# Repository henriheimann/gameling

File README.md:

# Gameling

A primitive handheld gaming console I build just for the sake of it. Comes with a backlight monochrome Nokia 5110 clip on display with a resolution of 84 times 48 pixels, 12 buttons that can be individually lit up and a piezo buzzer.

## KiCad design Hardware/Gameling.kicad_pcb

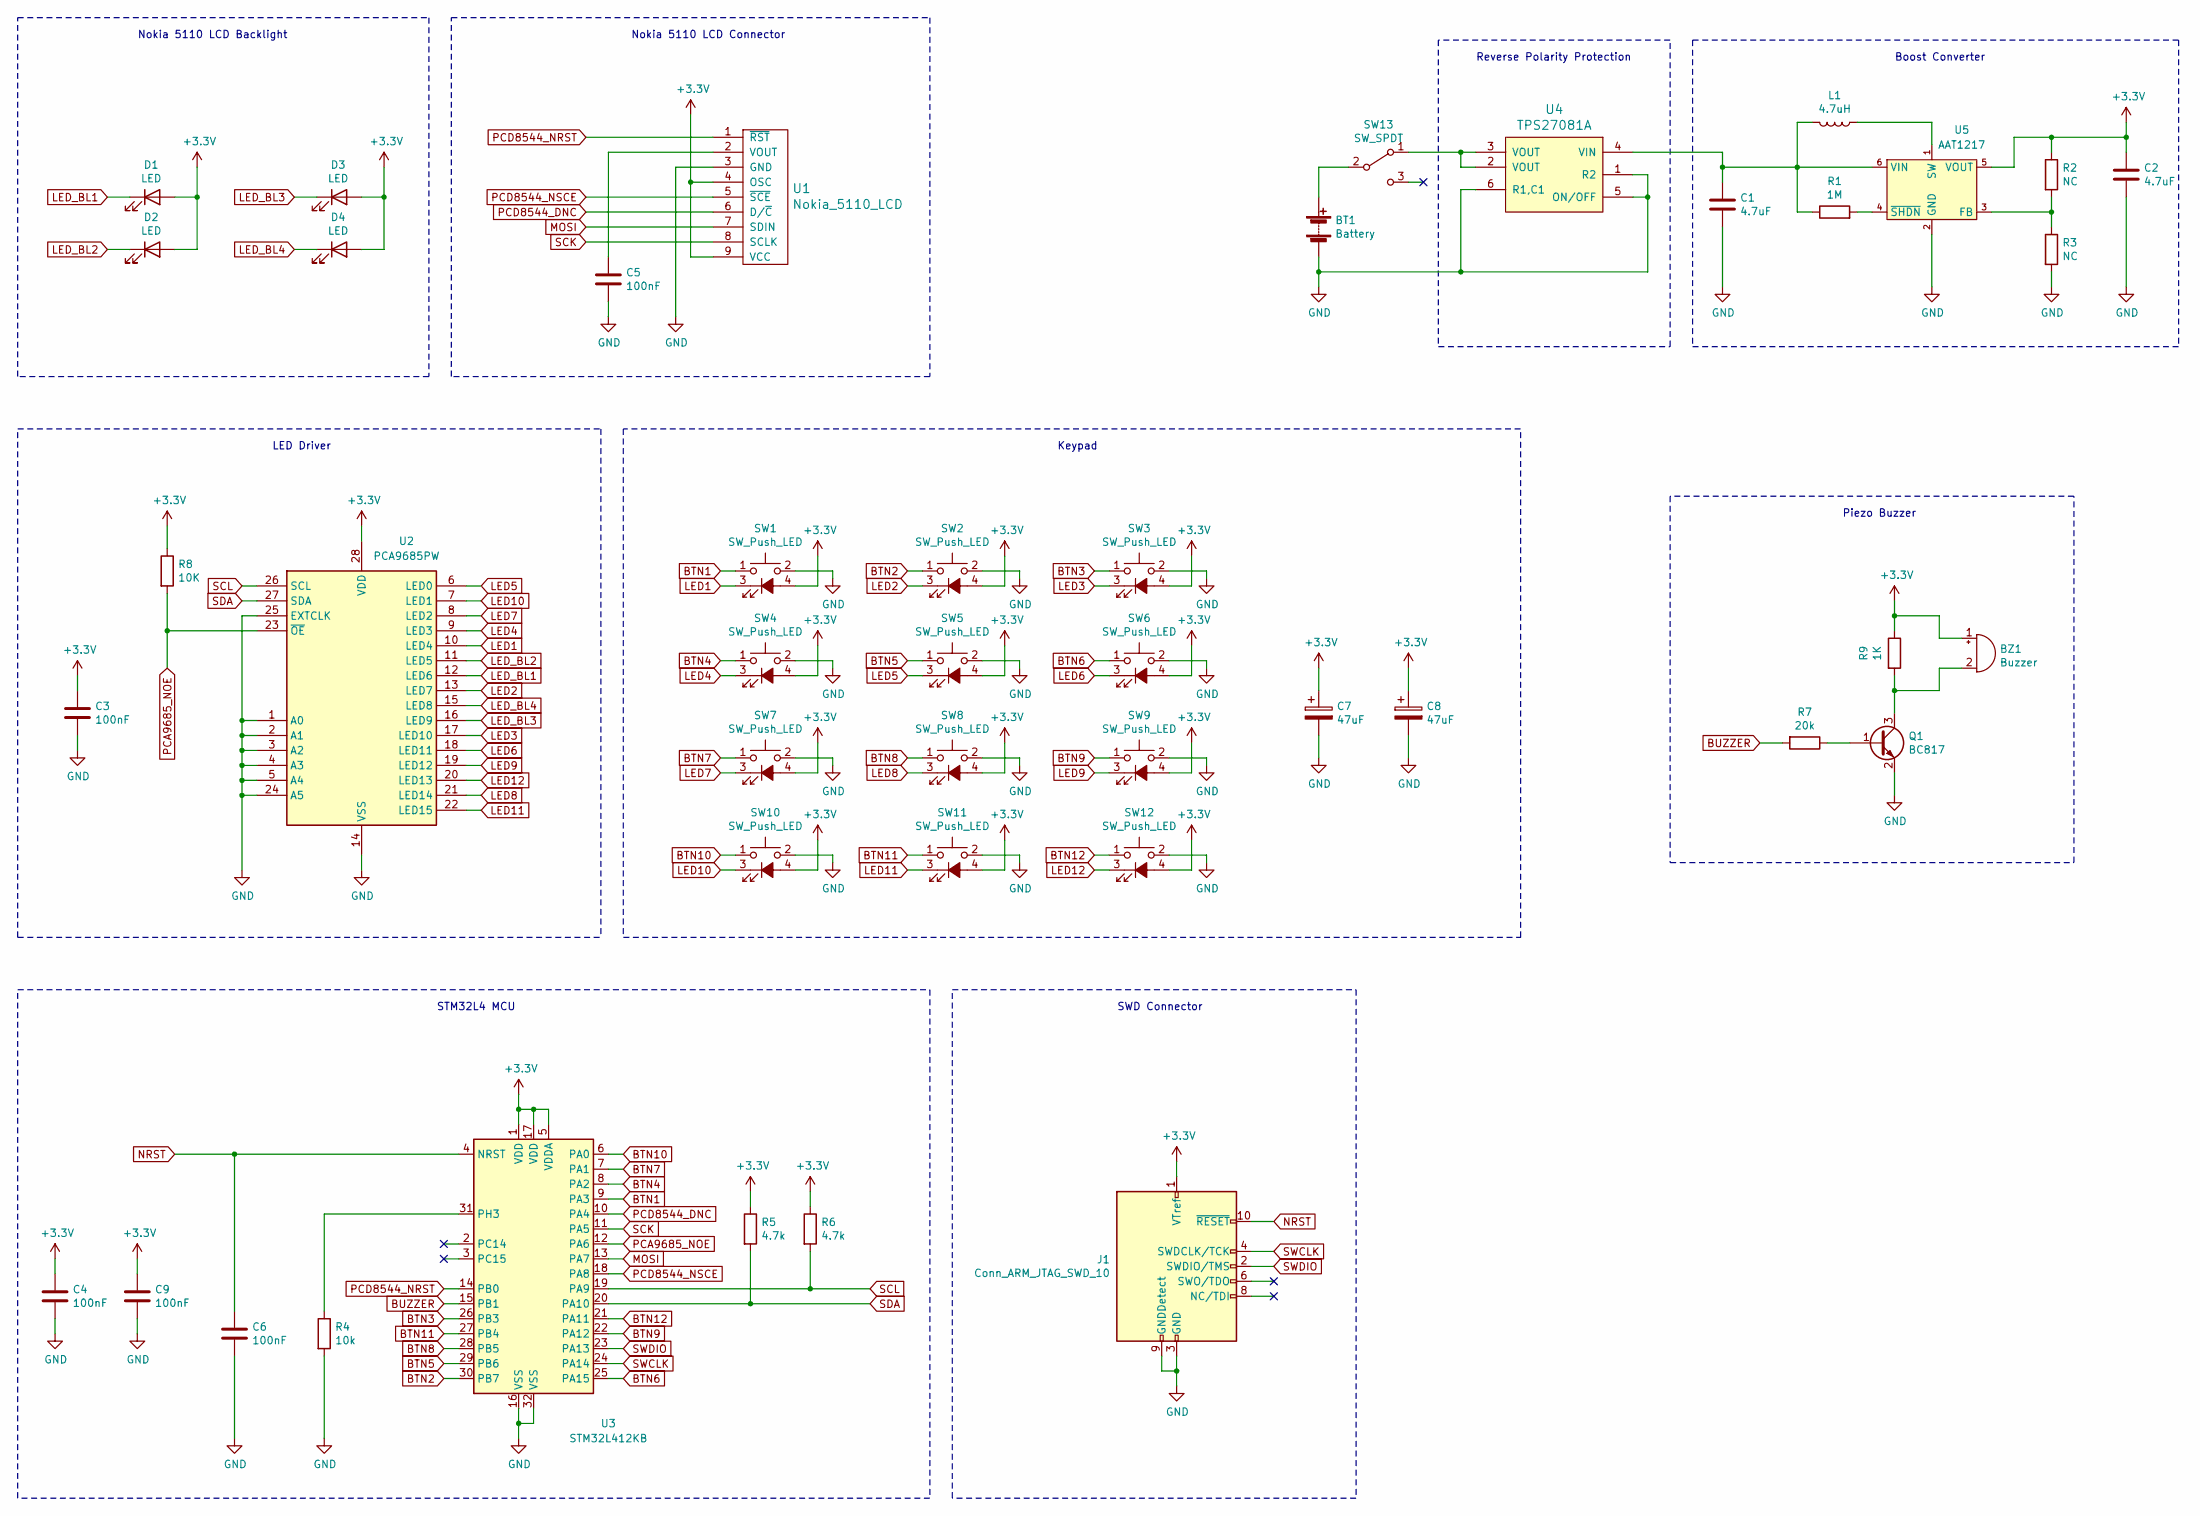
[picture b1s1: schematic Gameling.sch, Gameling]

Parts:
BT1: Battery; BatteryHolder_Keystone_2468_2xAAA_NoSilkscreen
BZ1: Buzzer; Buzzer_CUI_CPT-9019S-SMT_With3DModel
C1, C2: 4.7uF; C_0805_2012Metric_Pad1.15x1.40mm_HandSolder
C3, C4, C5, C6, C9: 100nF; C_0805_2012Metric_Pad1.15x1.40mm_HandSolder
C7, C8: 47uF; CP_Elec_4x4.5
D1, D2, D3, D4: LED; D_0805_2012Metric_Pad1.15x1.40mm_HandSolder_NoSilkscreen
J1: Conn_ARM_JTAG_SWD_10; Amphenol_FCI_ShroudedSocket_2x05_P1.27mm_Vertical_SMD
L1: 4.7uH; L_Bourns-SRN4018_With3DModel
Q1: BC817; SOT-23
R1: 1M; R_0805_2012Metric_Pad1.15x1.40mm_HandSolder
R2, R3: NC; R_0805_2012Metric_Pad1.15x1.40mm_HandSolder
R4: 10k; R_0805_2012Metric_Pad1.15x1.40mm_HandSolder
R5, R6: 4.7k; R_0805_2012Metric_Pad1.15x1.40mm_HandSolder
R7: 20k; R_0805_2012Metric_Pad1.15x1.40mm_HandSolder
R8: 10K; R_0805_2012Metric_Pad1.15x1.40mm_HandSolder
R9: 1K; R_0805_2012Metric_Pad1.15x1.40mm_HandSolder
SW1, SW2, SW3, SW4, SW5, SW6, SW7, SW8, SW9, SW10, SW11, SW12: SW_Push_LED; Generic_LED_Tactile_Button
SW13: SW_SPDT; SW_CuK_OS102011MA1QN1_SPDT_Angled_With3DModel_NoSilkscreen
U1: Nokia_5110_LCD; Nokia_5110-3310_LCD_NoSilkscreen
U2: PCA9685PW; TSSOP-28_4.4x9.7mm_P0.65mm
U3: STM32L412KB; LQFP-32_7x7mm_P0.8mm
U4: TPS27081A; TSOT-23-6_HandSoldering
U5: AAT1217; TSOT-23-6_HandSoldering

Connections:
+3V3: BZ1.1 (-), C2.1, C3.1, C4.1, C7.1, C8.1, C9.1, D1.2 (A), D2.2 (A), D3.2 (A), D4.2 (A), J1.1 (VTref), R2.1, R5.1, R6.1, R8.1, R9.1, SW1.4 (A), SW2.4 (A), SW3.4 (A), SW4.4 (A), SW5.4 (A), SW6.4 (A), SW7.4 (A), SW8.4 (A), SW9.4 (A), SW10.4 (A), SW11.4 (A), SW12.4 (A), U1.4 (OSC), U1.9 (VCC), U2.28 (VDD), U3.1 (VDD), U3.5 (VDDA), U3.17 (VDD), U5.5 (VOUT)
BTN1: SW1.1, U3.9 (PA3)
BTN2: SW2.1, U3.30 (PB7)
BTN3: SW3.1, U3.26 (PB3)
BTN4: SW4.1, U3.8 (PA2)
BTN5: SW5.1, U3.29 (PB6)
BTN6: SW6.1, U3.25 (PA15)
BTN7: SW7.1, U3.7 (PA1)
BTN8: SW8.1, U3.28 (PB5)
BTN9: SW9.1, U3.22 (PA12)
BTN10: SW10.1, U3.6 (PA0)
BTN11: SW11.1, U3.27 (PB4)
BTN12: SW12.1, U3.21 (PA11)
BUZZER: R7.2, U3.15 (PB1)
GND: BT1.2 (-), C1.2, C2.2, C3.2, C4.2, C5.2, C6.2, C7.2, C8.2, C9.2, J1.3 (GND), J1.5 (GND), J1.9 (GNDDetect), Q1.2 (E), R3.2, R4.2, SW1.2, SW2.2, SW3.2, SW4.2, SW5.2, SW6.2, SW7.2, SW8.2, SW9.2, SW10.2, SW11.2, SW12.2, U1.3 (GND), U2.1 (A0), U2.2 (A1), U2.3 (A2), U2.4 (A3), U2.5 (A4), U2.14 (VSS), U2.24 (A5), U2.25 (EXTCLK), U3.16 (VSS), U3.32 (VSS), U4.1 (R2), U4.5 (ON/OFF), U4.6 (R1,C1), U5.2 (GND)
LED1: SW1.3 (K), U2.10 (LED4)
LED2: SW2.3 (K), U2.13 (LED7)
LED3: SW3.3 (K), U2.17 (LED10)
LED4: SW4.3 (K), U2.9 (LED3)
LED5: SW5.3 (K), U2.6 (LED0)
LED6: SW6.3 (K), U2.18 (LED11)
LED7: SW7.3 (K), U2.8 (LED2)
LED8: SW8.3 (K), U2.21 (LED14)
LED9: SW9.3 (K), U2.19 (LED12)
LED10: SW10.3 (K), U2.7 (LED1)
LED11: SW11.3 (K), U2.22 (LED15)
LED12: SW12.3 (K), U2.20 (LED13)
LED_BL1: D1.1 (K), U2.12 (LED6)
LED_BL2: D2.1 (K), U2.11 (LED5)
LED_BL3: D3.1 (K), U2.16 (LED9)
LED_BL4: D4.1 (K), U2.15 (LED8)
MOSI: U1.7 (SDIN), U3.13 (PA7)
NRST: C6.1, J1.10 (~RESET~), U3.4 (NRST)
unnamed: BT1.1 (+), SW13.2 (B)
unnamed: BZ1.2 (+), Q1.3 (C), R9.2
unnamed: C1.1, L1.2, R1.1, U4.4 (VIN), U5.6 (VIN)
unnamed: C5.1, U1.2 (VOUT)
unnamed: L1.1, U5.1 (SW)
unnamed: Q1.1 (B), R7.1
unnamed: R1.2, U5.4 (~SHDN)
unnamed: R2.2, R3.1, U5.3 (FB)
unnamed: R4.1, U3.31 (PH3)
unnamed: SW13.1 (A), U4.2 (VOUT), U4.3 (VOUT)
PCA9685_NOE: R8.2, U2.23 (~OE), U3.12 (PA6)
PCD8544_DNC: U1.6 (D/~C), U3.10 (PA4)
PCD8544_NRST: U1.1 (~RST), U3.14 (PB0)
PCD8544_NSCE: U1.5 (~SCE), U3.18 (PA8)
SCK: U1.8 (SCLK), U3.11 (PA5)
SCL: R6.2, U2.26 (SCL), U3.19 (PA9)
SDA: R5.2, U2.27 (SDA), U3.20 (PA10)
SWCLK: J1.4 (SWDCLK/TCK), U3.24 (PA14)
SWDIO: J1.2 (SWDIO/TMS), U3.23 (PA13)

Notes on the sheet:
Reverse Polarity Protection
Boost Converter
STM32L4 MCU
SWD Connector
Nokia 5110 LCD Backlight
Nokia 5110 LCD Connector
LED Driver
Keypad
Piezo Buzzer

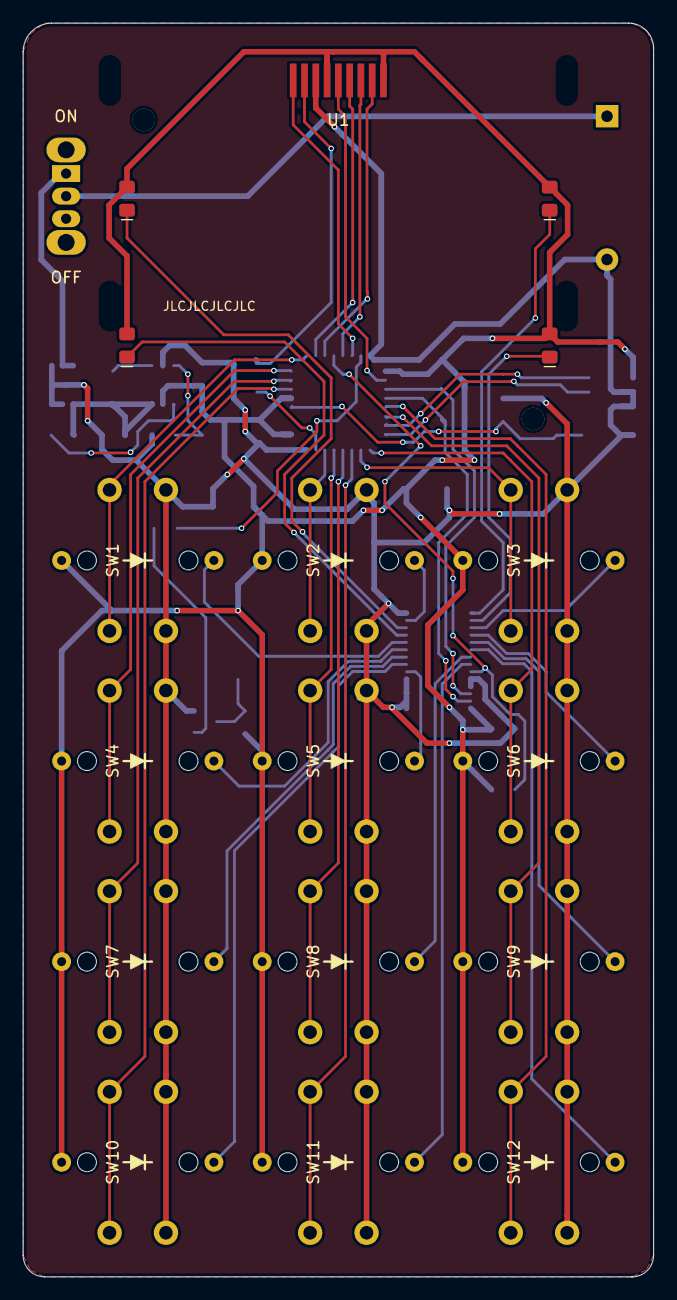
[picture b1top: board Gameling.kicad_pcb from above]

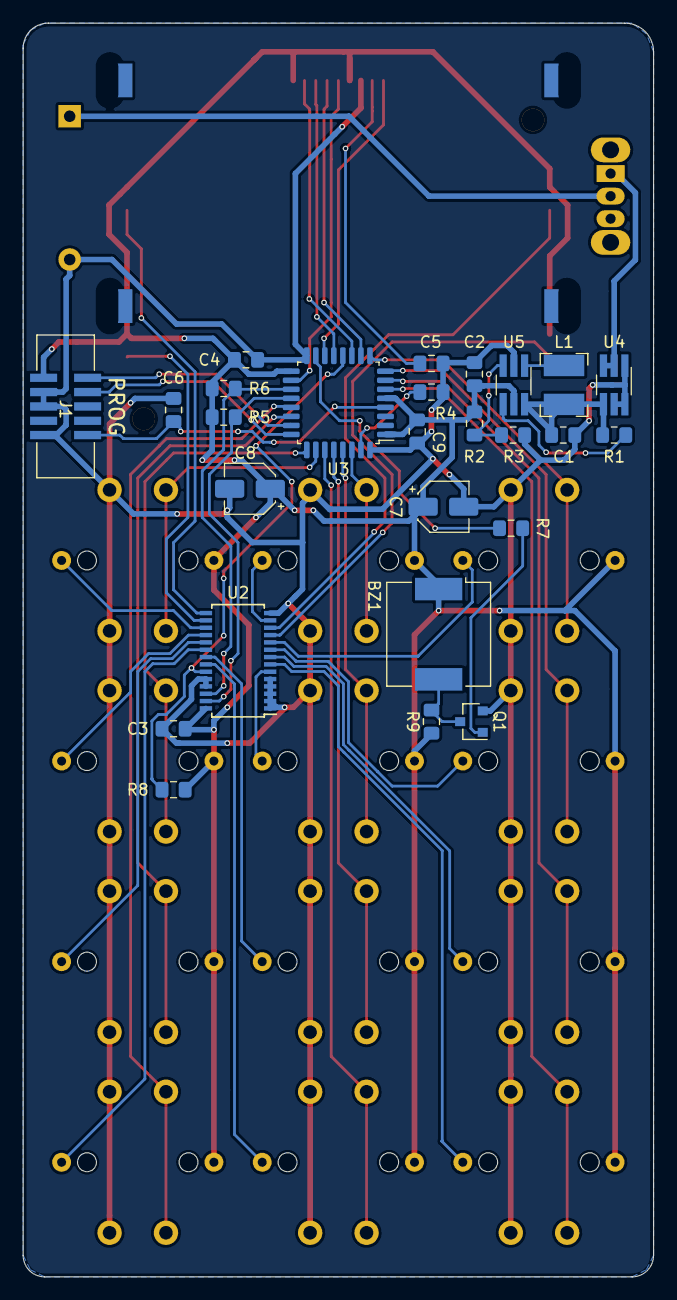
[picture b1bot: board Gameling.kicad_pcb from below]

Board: 2 copper layers, 55.9 x 111.1 mm, 45 parts (27 on the bottom side), 52 nets.

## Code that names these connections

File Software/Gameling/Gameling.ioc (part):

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Mcu.Name=STM32L412KBTx
Mcu.Package=LQFP32
Mcu.UserName=STM32L412KBTx
PA0-CK_IN.GPIOParameters=GPIO_PuPd,GPIO_Label
PA0-CK_IN.GPIO_Label=BUTTON_10
PA0-CK_IN.GPIO_PuPd=GPIO_PULLUP
PA0-CK_IN.Signal=GPIO_Input
PA1.GPIOParameters=GPIO_PuPd,GPIO_Label
PA1.GPIO_Label=BUTTON_7
PA1.GPIO_PuPd=GPIO_PULLUP
PA1.Signal=GPIO_Input
PA10.Mode=I2C
PA10.Signal=I2C1_SDA
PA11.GPIOParameters=GPIO_PuPd,GPIO_Label
PA11.GPIO_Label=BUTTON_12
PA11.GPIO_PuPd=GPIO_PULLUP
PA11.Signal=GPIO_Input
PA12.GPIOParameters=GPIO_PuPd,GPIO_Label
PA12.GPIO_Label=BUTTON_9
PA12.GPIO_PuPd=GPIO_PULLUP
PA12.Signal=GPIO_Input
PA13\ (JTMS/SWDIO).Mode=Serial_Wire
PA13\ (JTMS/SWDIO).Signal=SYS_JTMS-SWDIO
PA14\ (JTCK/SWCLK).Mode=Serial_Wire
PA14\ (JTCK/SWCLK).Signal=SYS_JTCK-SWCLK
PA15\ (JTDI).GPIOParameters=GPIO_PuPd,GPIO_Label
PA15\ (JTDI).GPIO_Label=BUTTON_6
PA15\ (JTDI).GPIO_PuPd=GPIO_PULLUP
PA15\ (JTDI).Signal=GPIO_Input
PA2.GPIOParameters=GPIO_PuPd,GPIO_Label
PA2.GPIO_Label=BUTTON_4
PA2.GPIO_PuPd=GPIO_PULLUP
PA2.Signal=GPIO_Input
PA3.GPIOParameters=GPIO_PuPd,GPIO_Label
PA3.GPIO_Label=BUTTON_1
PA3.GPIO_PuPd=GPIO_PULLUP
PA3.Signal=GPIO_Input
PA4.GPIOParameters=GPIO_PuPd,GPIO_Label
PA4.GPIO_Label=NOKIA5110_DNC
PA4.GPIO_PuPd=GPIO_PULLDOWN
PA4.Signal=GPIO_Output
PA5.GPIOParameters=GPIO_PuPd
PA5.GPIO_PuPd=GPIO_PULLDOWN
PA5.Mode=Simplex_Bidirectional_Master
PA5.Signal=SPI1_SCK
PA7.GPIOParameters=GPIO_PuPd
PA7.GPIO_PuPd=GPIO_PULLDOWN
PA7.Mode=Simplex_Bidirectional_Master
PA7.Signal=SPI1_MOSI
PA8.GPIOParameters=GPIO_PuPd,GPIO_Label
PA8.GPIO_Label=NOKIA5110_NSCE
PA8.GPIO_PuPd=GPIO_PULLDOWN
PA8.Signal=GPIO_Output
PA9.Mode=I2C
PA9.Signal=I2C1_SCL
PB0.GPIOParameters=GPIO_PuPd,GPIO_Label
PB0.GPIO_Label=NOKIA5110_NRST
PB0.GPIO_PuPd=GPIO_PULLUP
PB0.Signal=GPIO_Output
PB1.GPIOParameters=GPIO_Label
PB1.GPIO_Label=BUZZER
PB1.Mode=PWM Generation3 CH3N
PB1.Signal=TIM1_CH3N
PB3\ (JTDO/TRACESWO).GPIOParameters=GPIO_PuPd,GPIO_Label
PB3\ (JTDO/TRACESWO).GPIO_Label=BUTTON_3
PB3\ (JTDO/TRACESWO).GPIO_PuPd=GPIO_PULLUP
PB3\ (JTDO/TRACESWO).Signal=GPIO_Input
PB4\ (NJTRST).GPIOParameters=GPIO_PuPd,GPIO_Label
PB4\ (NJTRST).GPIO_Label=BUTTON_11
PB4\ (NJTRST).GPIO_PuPd=GPIO_PULLUP
PB4\ (NJTRST).Signal=GPIO_Input
PB5.GPIOParameters=GPIO_PuPd,GPIO_Label
PB5.GPIO_Label=BUTTON_8
PB5.GPIO_PuPd=GPIO_PULLUP
PB5.Signal=GPIO_Input
PB6.GPIOParameters=GPIO_PuPd,GPIO_Label
PB6.GPIO_Label=BUTTON_5
PB6.GPIO_PuPd=GPIO_PULLUP
PB6.Signal=GPIO_Input
PB7.GPIOParameters=GPIO_PuPd,GPIO_Label
PB7.GPIO_Label=BUTTON_2
PB7.GPIO_PuPd=GPIO_PULLUP
PB7.Signal=GPIO_Input
RCC.HSE_VALUE=8000000
RCC.SYSCLKFreq_VALUE=16000000
RCC.SYSCLKSource=RCC_SYSCLKSOURCE_PLLCLK
board=custom

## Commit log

2020-04-22 Add README and picture
2020-04-22 Scale image
2020-04-23 Adjust LED brightnesses
2020-04-23 Add multi application logic
2020-04-23 Add intro notes, fix first song segment not being played
2020-04-23 Add LED countdown during intro, function to set all button LEDs at once
2020-05-24 Add main menu
2020-10-17 Update to new symbol and footprints libraries
2020-10-19 Move embedded project to subfolder for CLion
2020-10-19 Remove old submodule contents
2020-10-19 Readd pca9685 submodule
2020-10-19 Readd pcd8544 submodule
2020-12-28 Update submodules remotes
